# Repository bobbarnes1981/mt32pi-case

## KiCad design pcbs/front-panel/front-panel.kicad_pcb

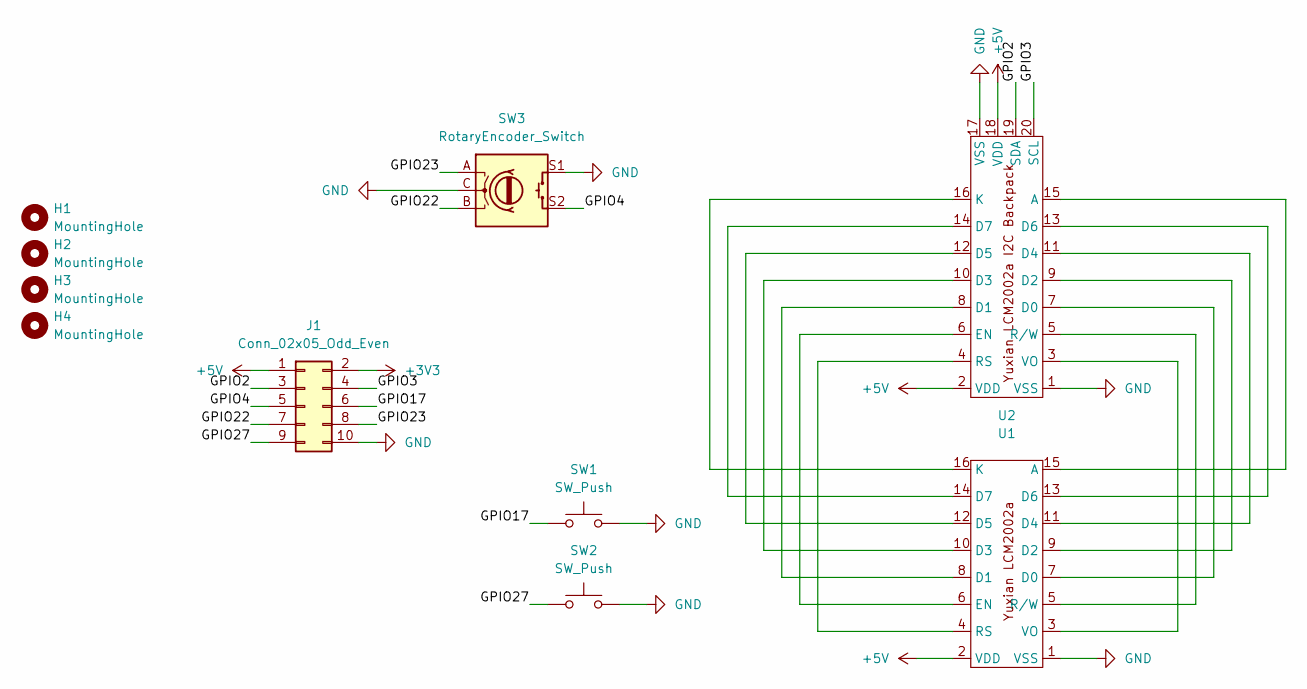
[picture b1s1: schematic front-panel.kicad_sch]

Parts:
H1, H2, H3, H4: MountingHole; MountingHole_3.2mm_M3_DIN965_Pad
J1: Conn_02x05_Odd_Even; IDC-Header_2x05_P2.54mm_Vertical
SW1, SW2: SW_Push; SW_Cherry_MX_1.00u_PCB
SW3: RotaryEncoder_Switch; RotaryEncoder_Alps_EC11E-Switch_Vertical_H20mm_MountingHoles
U1: Yuxian LCM2002a
U2: Yuxian LCM2002a I2C Backpack

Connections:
+3V3: J1.2
+5V: J1.1, U1.2 (VDD), U2.2 (VDD), U2.18 (VDD)
/GPIO2: J1.3, U2.19 (SDA)
/GPIO3: J1.4, U2.20 (SCL)
/GPIO4: J1.5, SW3.S2
/GPIO17: J1.6, SW1.1
/GPIO22: J1.7, SW3.B
/GPIO23: J1.8, SW3.A
/GPIO27: J1.9, SW2.1
GND: J1.10, SW1.2, SW2.2, SW3.C, SW3.S1, U1.1 (VSS), U2.1 (VSS), U2.17 (VSS)
unnamed: U1.15 (A), U2.15 (A)
unnamed: U1.7 (D0), U2.7 (D0)
unnamed: U1.8 (D1), U2.8 (D1)
unnamed: U1.9 (D2), U2.9 (D2)
unnamed: U1.10 (D3), U2.10 (D3)
unnamed: U1.11 (D4), U2.11 (D4)
unnamed: U1.12 (D5), U2.12 (D5)
unnamed: U1.13 (D6), U2.13 (D6)
unnamed: U1.14 (D7), U2.14 (D7)
unnamed: U1.6 (EN), U2.6 (EN)
unnamed: U1.16 (K), U2.16 (K)
unnamed: U1.4 (RS), U2.4 (RS)
unnamed: U1.5 (R/W), U2.5 (R/W)
unnamed: U1.3 (VO), U2.3 (VO)

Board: 2 copper layers, 10 parts (2 on the bottom side), 23 nets, no tracks yet.

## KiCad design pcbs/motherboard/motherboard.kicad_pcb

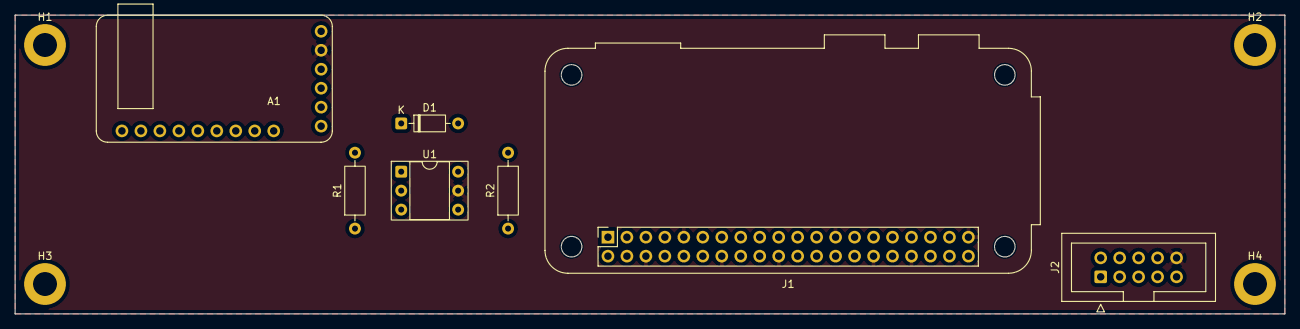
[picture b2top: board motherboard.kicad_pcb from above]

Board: 2 copper layers, 170.0 x 40.0 mm, 11 parts (0 on the bottom side), 16 nets, no tracks yet.

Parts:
A1: GY-PCM5102
D1: 1N4148; D_DO-35_SOD27_P7.62mm_Horizontal
H1, H2, H3, H4: MountingHole; MountingHole_3.2mm_M3_DIN965_Pad
J1: Raspberry_Pi_4; Raspberry_Pi_Zero_Socketed_THT_FaceDown_MountingHoles
J2: Conn_02x05_Odd_Even; IDC-Header_2x05_P2.54mm_Vertical
R1: 220R; R_Axial_DIN0207_L6.3mm_D2.5mm_P10.16mm_Horizontal
R2: 1k; R_Axial_DIN0207_L6.3mm_D2.5mm_P10.16mm_Horizontal
U1: H11L1; DIP-6_W7.62mm_Socket

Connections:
+3V3: A1.6 (VIN), J1.1 (3V3), J1.17 (3V3), J2.2, R2.2, U1.6
+5V: J1.2 (5V), J1.4 (5V), J2.1
/GPIO2: J1.3 (SDA_I2C1/GPIO02), J2.3
/GPIO3: J1.5 (SCL_I2C1/GPIO03), J2.4
/GPIO4: J1.7 (GPCLK0/GPIO04), J2.5
/GPIO15: J1.10 (GPIO15/UART_RXD), R2.1, U1.4
/GPIO17: J1.11 (GPIO17/SPI1_~CE1), J2.6
/GPIO18: A1.2 (BCK), J1.12 (GPIO18/SPI1_~CE0/PCM_CLK/PWM0)
/GPIO19: A1.4 (LCK), J1.35 (GPIO19/SPI1_MISO/PCM_FS)
/GPIO21: A1.3 (DIN), J1.40 (GPIO21/SPI1_SCLK/PCM_DOUT)
/GPIO22: J1.15 (GPIO22/SDIO_CLK), J2.7
/GPIO23: J1.16 (GPIO23/SDIO_CMD), J2.8
/GPIO27: J1.13 (GPIO27/SDIO_DAT3), J2.9
/MIDI_OUT: D1.2 (A), U1.2
GND: A1.5 (GND), J1.6 (GND), J1.9 (GND), J1.14 (GND), J1.20 (GND), J1.25 (GND), J1.30 (GND), J1.34 (GND), J1.39 (GND), J2.10, U1.5
unnamed: D1.1 (K), R1.2, U1.1
